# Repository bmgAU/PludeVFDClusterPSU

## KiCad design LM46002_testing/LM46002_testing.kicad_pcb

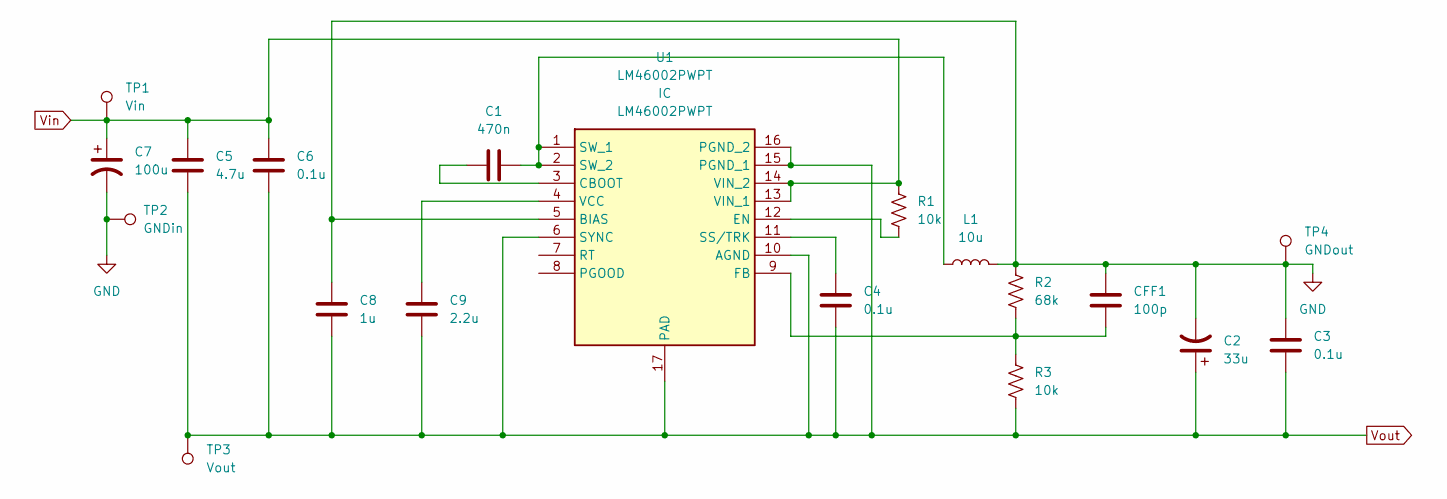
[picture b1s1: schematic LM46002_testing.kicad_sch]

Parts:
C1: 470n; C_0603_1608Metric
C2: 33u; CP_Elec_6.3x9.9
C3, C4, C6: 0.1u; C_0603_1608Metric
C5: 4.7u; C_1210_3225Metric
C7: 100u; CP_Elec_10x10.5
C8: 1u; C_0603_1608Metric
C9: 2.2u; C_0603_1608Metric
CFF1: 100p; C_0603_1608Metric
L1: 10u; L_Taiyo-Yuden_NR-10050_9.8x10.0mm
R1, R3: 10k; R_0603_1608Metric
R2: 68k; R_0603_1608Metric
TP1: Vin; TestPoint_Keystone_5010-5014_Multipurpose
TP2: GNDin; TestPoint_Keystone_5010-5014_Multipurpose
TP3: Vout; TestPoint_Keystone_5010-5014_Multipurpose
TP4: GNDout; TestPoint_Keystone_5010-5014_Multipurpose
U1: LM46002PWPT; TI_HTSSOP-16_SOP65P640X120-17N; Mouser Part Number 595-LM46002PWPT

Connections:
GND: C2.2, C3.1, C7.2, C8.1, CFF1.1, L1.2, R2.1, TP2.1, TP4.1, U1.5 (BIAS)
unnamed: C1.1, U1.3 (CBOOT)
unnamed: C1.2, L1.1, U1.1 (SW_1), U1.2 (SW_2)
unnamed: C9.1, U1.4 (VCC)
unnamed: CFF1.2, R2.2, R3.1, U1.9 (FB)
unnamed: C4.1, U1.11 (SS/TRK)
unnamed: R1.2, U1.12 (EN)
Vin: C5.1, C6.1, C7.1, R1.1, TP1.1, U1.13 (VIN_1), U1.14 (VIN_2)
Vout: C2.1, C3.2, C4.2, C5.2, C6.2, C8.2, C9.2, R3.2, TP3.1, U1.6 (SYNC), U1.10 (AGND), U1.15 (PGND_1), U1.16 (PGND_2), U1.17 (PAD)

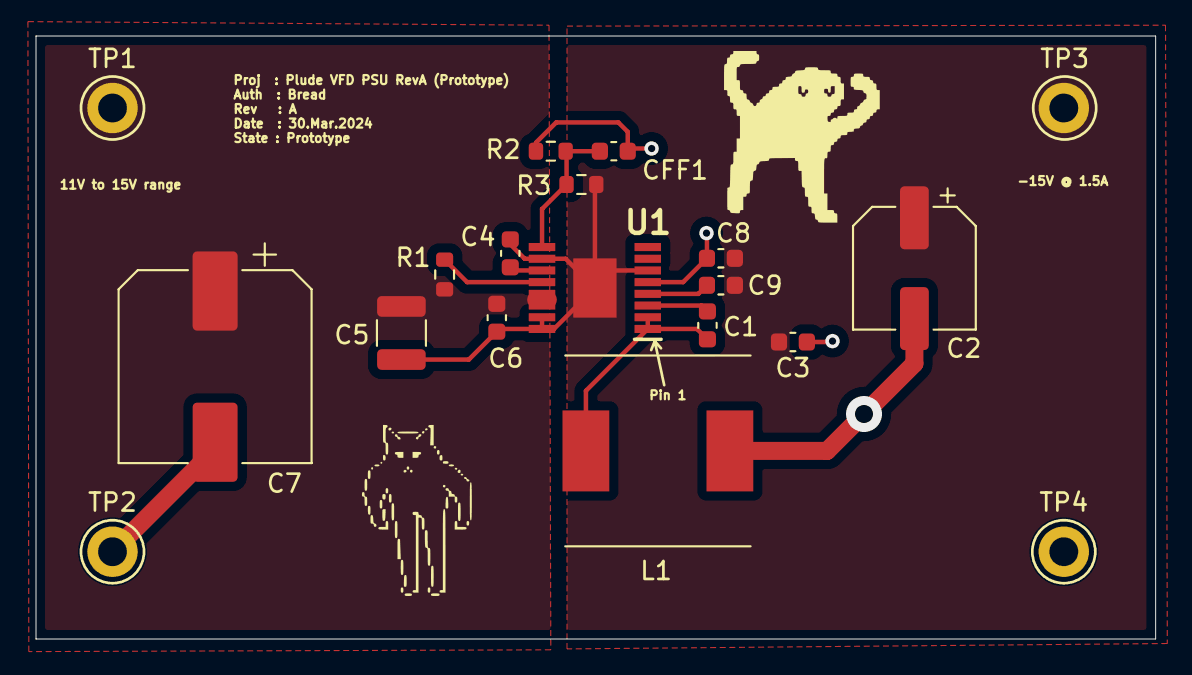
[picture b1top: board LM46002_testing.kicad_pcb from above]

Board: 2 copper layers, 62.2 x 33.5 mm, 19 parts (0 on the bottom side), 9 nets.
